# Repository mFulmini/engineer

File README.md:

# engineer
Tutaj znajduje się część pracy inżynierskiej w postaci oprogramowań jednostek brzegowych, rysunków, schematów elektrycznych oraz poglądowych zrzutów ekranu.  This section presents a part of the engineering thesis, comprising edge unit software, technical drawings, electrical schematics, and illustrative screenshots.

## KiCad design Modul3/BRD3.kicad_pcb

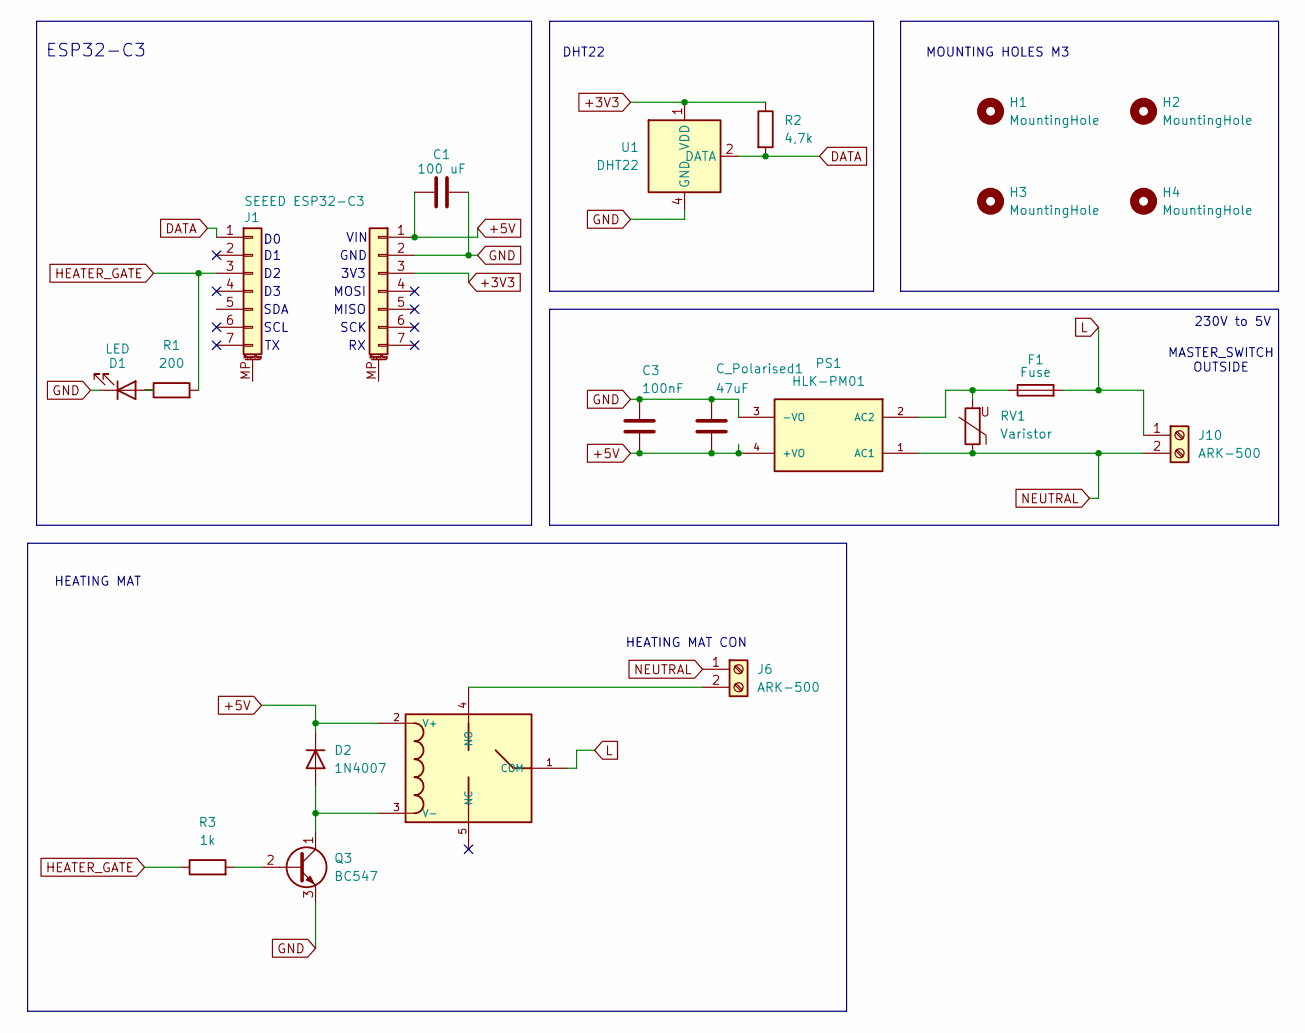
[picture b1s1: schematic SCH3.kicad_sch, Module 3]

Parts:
C1: 100 uF; CP_Radial_D5.0mm_P2.00mm
C3: 100nF; C_Disc_D5.0mm_W2.5mm_P2.50mm
C_Polarised1: 47uF; CP_Radial_D5.0mm_P2.00mm
D1: LED; LED_D5.0mm
D2: 1N4007; D_DO-41_SOD81_P10.16mm_Horizontal
F1: Fuse; Fuseholder_Cylinder-5x20mm_Schurter_FAB_0031-355x_Horizonta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
H1, H2, H3, H4: MountingHole; MountingHole_3.2mm_M3
J1: SEEED ESP32-C3; PinSocket_1x07_P2.54mm_Vertical
J4: Conn_01x07_MountingPin; PinSocket_1x07_P2.54mm_Vertical
J6, J10: ARK-500; TerminalBlock_MaiXu_MX126-5.0-02P_1x02_P5.00mm
K1: RELAY-HLS8L-DC5V-S-C_5P-19X15MM_; REY5-19.0X15.0X15.0MM; MPN HLS8L-DC5V-S-C
PS1: HLK-PM01; Converter_ACDC_Hi-Link_HLK-PMxx
Q3: BC547; TO-92_Inline
R1: 200; R_Axial_DIN0207_L6.3mm_D2.5mm_P5.08mm_Vertical
R2: 4,7k; R_Axial_DIN0207_L6.3mm_D2.5mm_P5.08mm_Vertical
R3: 1k; R_Axial_DIN0207_L6.3mm_D2.5mm_P5.08mm_Vertical
RV1: Varistor; RV_Disc_D9mm_W3.6mm_P5mm
U1: DHT22; PinSocket_1x04_P2.54mm_Vertical

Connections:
+3V3: J4.3, R2.1, U1.1 (VDD)
+5V: C1.1, C3.2, C_Polarised1.2, D2.1 (K), J4.1, K1.2 (V+), PS1.4 (+VO)
DATA: J1.1, R2.2, U1.2 (DATA)
GND: C1.2, C3.1, C_Polarised1.1, D1.1 (K), J4.2, PS1.3 (-VO), Q3.3 (E), U1.4 (GND)
HEATER_GATE: J1.3, R1.2, R3.1
L: F1.2, J10.1, K1.1 (COM)
NEUTRAL: J6.1, J10.2, PS1.1 (AC1), RV1.1
unnamed: D1.2 (A), R1.1
unnamed: D2.2 (A), K1.3 (V-), Q3.1 (C)
unnamed: J6.2, K1.4 (NO)
unnamed: F1.1, PS1.2 (AC2), RV1.2
unnamed: Q3.2 (B), R3.2

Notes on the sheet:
SDA
HEATING MAT
VIN
GND
HEATING MAT CON
MASTER_SWITCH OUTSIDE
SCL
ESP32-C3
DHT22
SCK
MOSI
3V3
MOUNTING HOLES M3
MISO
230V to 5V

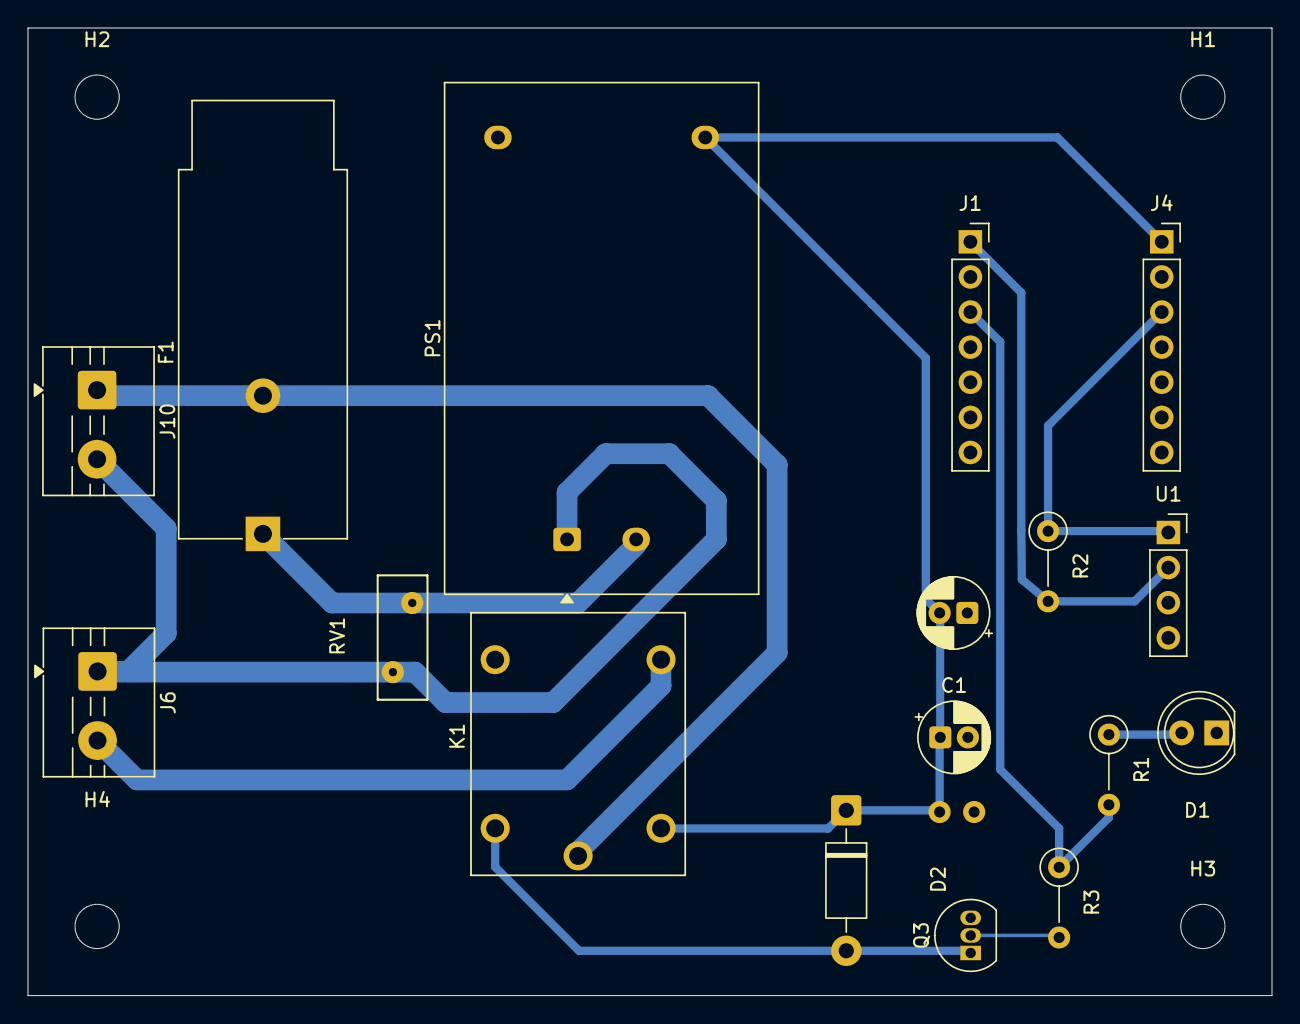
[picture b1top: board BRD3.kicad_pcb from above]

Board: 2 copper layers, 90.0 x 70.0 mm, 22 parts (1 on the bottom side), 12 nets.

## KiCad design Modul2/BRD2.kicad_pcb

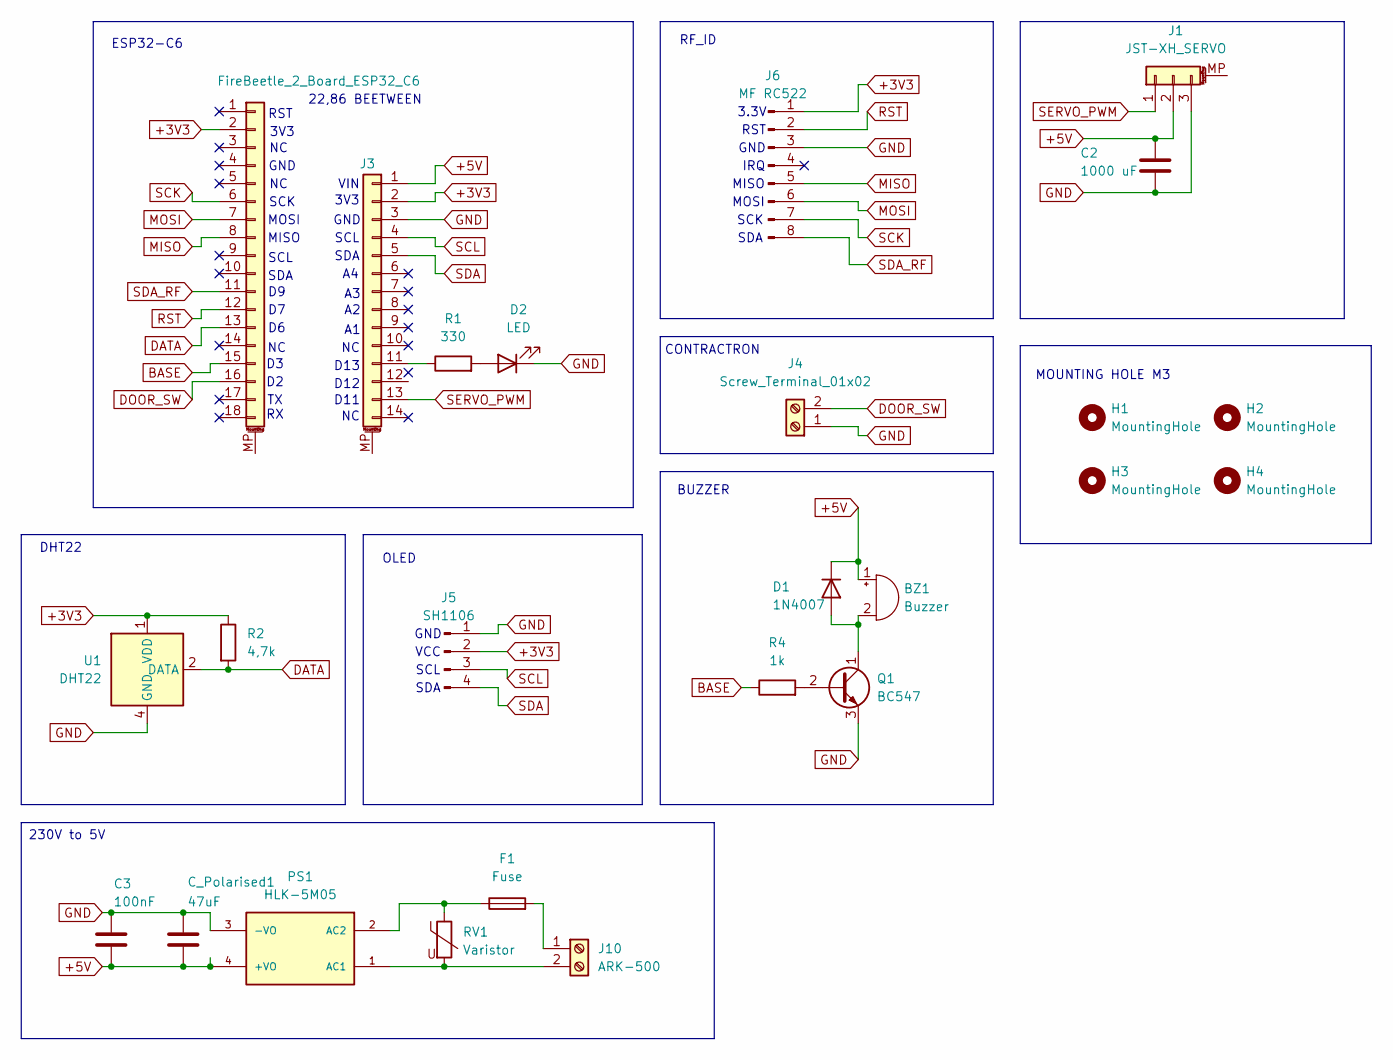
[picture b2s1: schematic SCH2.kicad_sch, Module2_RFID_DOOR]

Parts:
BZ1: Buzzer; Buzzer_12x9.5RM7.6
C2: 1000 uF; CP_Radial_D7.5mm_P2.50mm
C3: 100nF; C_Disc_D3.0mm_W2.0mm_P2.50mm
C_Polarised1: 47uF; CP_Radial_D5.0mm_P2.00mm
D1: 1N4007; D_DO-41_SOD81_P10.16mm_Horizontal
D2: LED; LED_D5.0mm
F1: Fuse; Fuseholder_Cylinder-5x20mm_Schurter_FAB_0031-355x_Horizonta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
H1, H2, H3, H4: MountingHole; MountingHole_3.2mm_M3
J1: JST-XH_SERVO; PinHeader_1x03_P2.54mm_Horizontal
J2: Conn_01x18_MountingPin; PinSocket_1x18_P2.54mm_Vertical
J3: FireBeetle_2_Board_ESP32_C6; PinSocket_1x14_P2.54mm_Vertical
J4: Screw_Terminal_01x02; TerminalBlock_MaiXu_MX126-5.0-02P_1x02_P5.00mm
J5: SH1106; PinSocket_1x04_P2.54mm_Vertical
J6: MF RC522; PinSocket_1x08_P2.54mm_Vertical
J10: ARK-500; TerminalBlock_MaiXu_MX126-5.0-02P_1x02_P5.00mm
PS1: HLK-5M05; Converter_ACDC_Hi-Link_HLK-PMxx
Q1: BC547; TO-92_Inline
R1: 330; R_Axial_DIN0207_L6.3mm_D2.5mm_P10.16mm_Horizontal
R2: 4,7k; R_Axial_DIN0207_L6.3mm_D2.5mm_P7.62mm_Horizontal
R4: 1k; R_Axial_DIN0207_L6.3mm_D2.5mm_P7.62mm_Horizontal
RV1: Varistor; RV_Disc_D12mm_W3.9mm_P7.5mm
U1: DHT22; PinSocket_1x04_P2.54mm_Vertical

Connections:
+3V3: J2.2, J3.2, J5.2, J6.1, R2.1, U1.1 (VDD)
+5V: BZ1.1 (+), C2.1, C3.2, C_Polarised1.2, D1.1 (K), J1.2, J3.1, PS1.4 (+VO)
BASE: J2.15, R4.1
DATA: J2.13, R2.2, U1.2 (DATA)
DOOR_SW: J2.16, J4.2
GND: C2.2, C3.1, C_Polarised1.1, D2.1 (K), J1.3, J3.3, J4.1, J5.1, J6.3, PS1.3 (-VO), Q1.3 (E), U1.4 (GND)
MISO: J2.8, J6.5
MOSI: J2.7, J6.6
unnamed: BZ1.2 (-), D1.2 (A), Q1.1 (C)
unnamed: D2.2 (A), R1.2
unnamed: J3.11, R1.1
unnamed: F1.2, J10.1
unnamed: J10.2, PS1.1 (AC1), RV1.2
unnamed: F1.1, PS1.2 (AC2), RV1.1
unnamed: Q1.2 (B), R4.2
RST: J2.12, J6.2
SCK: J2.6, J6.7
SCL: J3.4, J5.3
SDA: J3.5, J5.4
SDA_RF: J2.11, J6.8
SERVO_PWM: J1.1, J3.13

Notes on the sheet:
VCC
GND
MOUNTING HOLE M3
3V3
IRQ
SCK
ESP32-C6
22,86 BEETWEEN
D13
RF_ID
D11
MOSI
SCL
SDA
BUZZER
CONTRACTRON
RST
GND
SCK
MISO
D12
VIN
OLED
DHT22
3.3V
230V to 5V

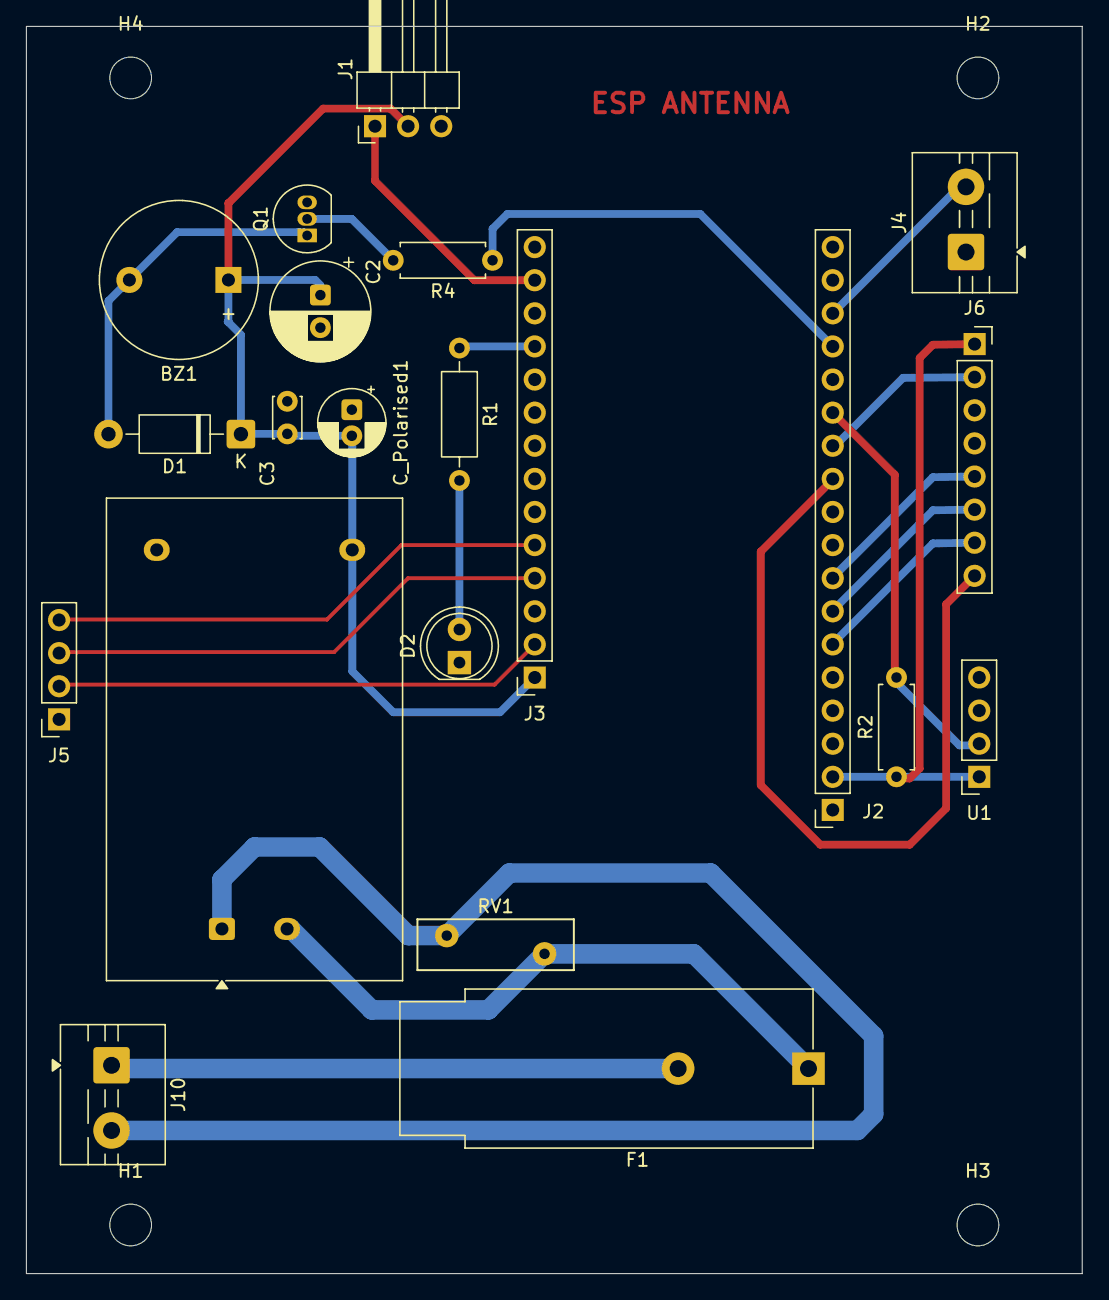
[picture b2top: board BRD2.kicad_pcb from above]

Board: 2 copper layers, 81.0 x 95.7 mm, 25 parts (0 on the bottom side), 21 nets.

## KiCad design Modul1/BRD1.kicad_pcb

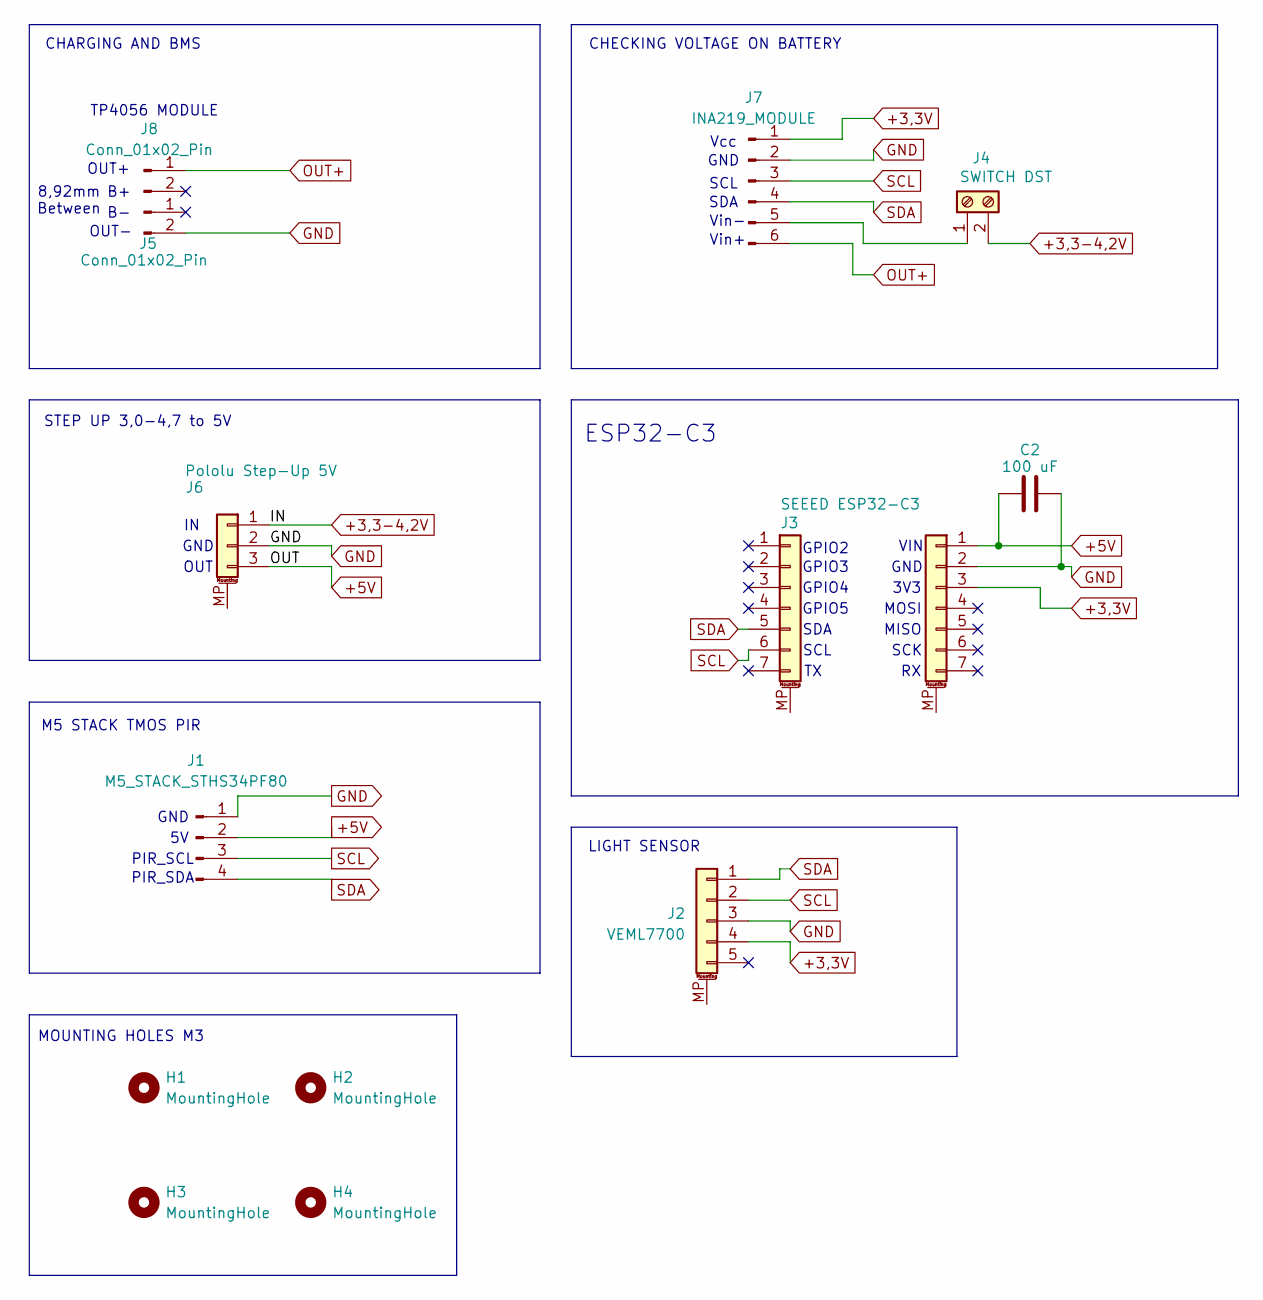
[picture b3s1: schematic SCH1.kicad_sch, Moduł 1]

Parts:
C2: 100 uF; CP_Radial_D5.0mm_P2.00mm
H1, H2, H3, H4: MountingHole; MountingHole_3.2mm_M3
J1: M5_STACK_STHS34PF80; JST_PH_B4B-PH-K_1x04_P2.00mm_Vertical
J2: VEML7700; PinSocket_1x05_P2.54mm_Vertical
J3: SEEED ESP32-C3; PinSocket_1x07_P2.54mm_Vertical
J4: SWITCH DST; TerminalBlock_MaiXu_MX126-5.0-02P_1x02_P5.00mm
J5, J8: Conn_01x02_Pin; PinHeader_1x02_P2.54mm_Vertical
J6: Pololu Step-Up 5V; PinHeader_1x03_P2.54mm_Vertical
J7: INA219_MODULE; PinHeader_1x06_P2.54mm_Vertical
J11: Conn_01x07_MountingPin; PinSocket_1x07_P2.54mm_Vertical

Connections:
+3,3-4,2V: J4.2, J6.1
+3,3V: J2.4, J7.1, J11.3
+5V: C2.1, J1.2, J6.3, J11.1
GND: C2.2, J1.1, J2.3, J5.2, J6.2, J7.2, J11.2
unnamed: J4.1, J7.5
OUT+: J7.6, J8.1
SCL: J1.3, J2.2, J3.6, J7.3
SDA: J1.4, J2.1, J3.5, J7.4

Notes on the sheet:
3V3
8,92mm Between
GND
LIGHT SENSOR
SCL
Vcc
OUT-
MOUNTING HOLES M3
MISO
M5 STACK TMOS PIR
GPIO5
VIN
CHARGING AND BMS
Vin+
SDA
MOSI
GPIO2
STEP UP 3,0-4,7 to 5V
ESP32-C3
TP4056 MODULE
PIR_SCL
OUT+
SCK
GPIO3
OUT
Vin-
PIR_SDA
GPIO4
CHECKING VOLTAGE ON BATTERY

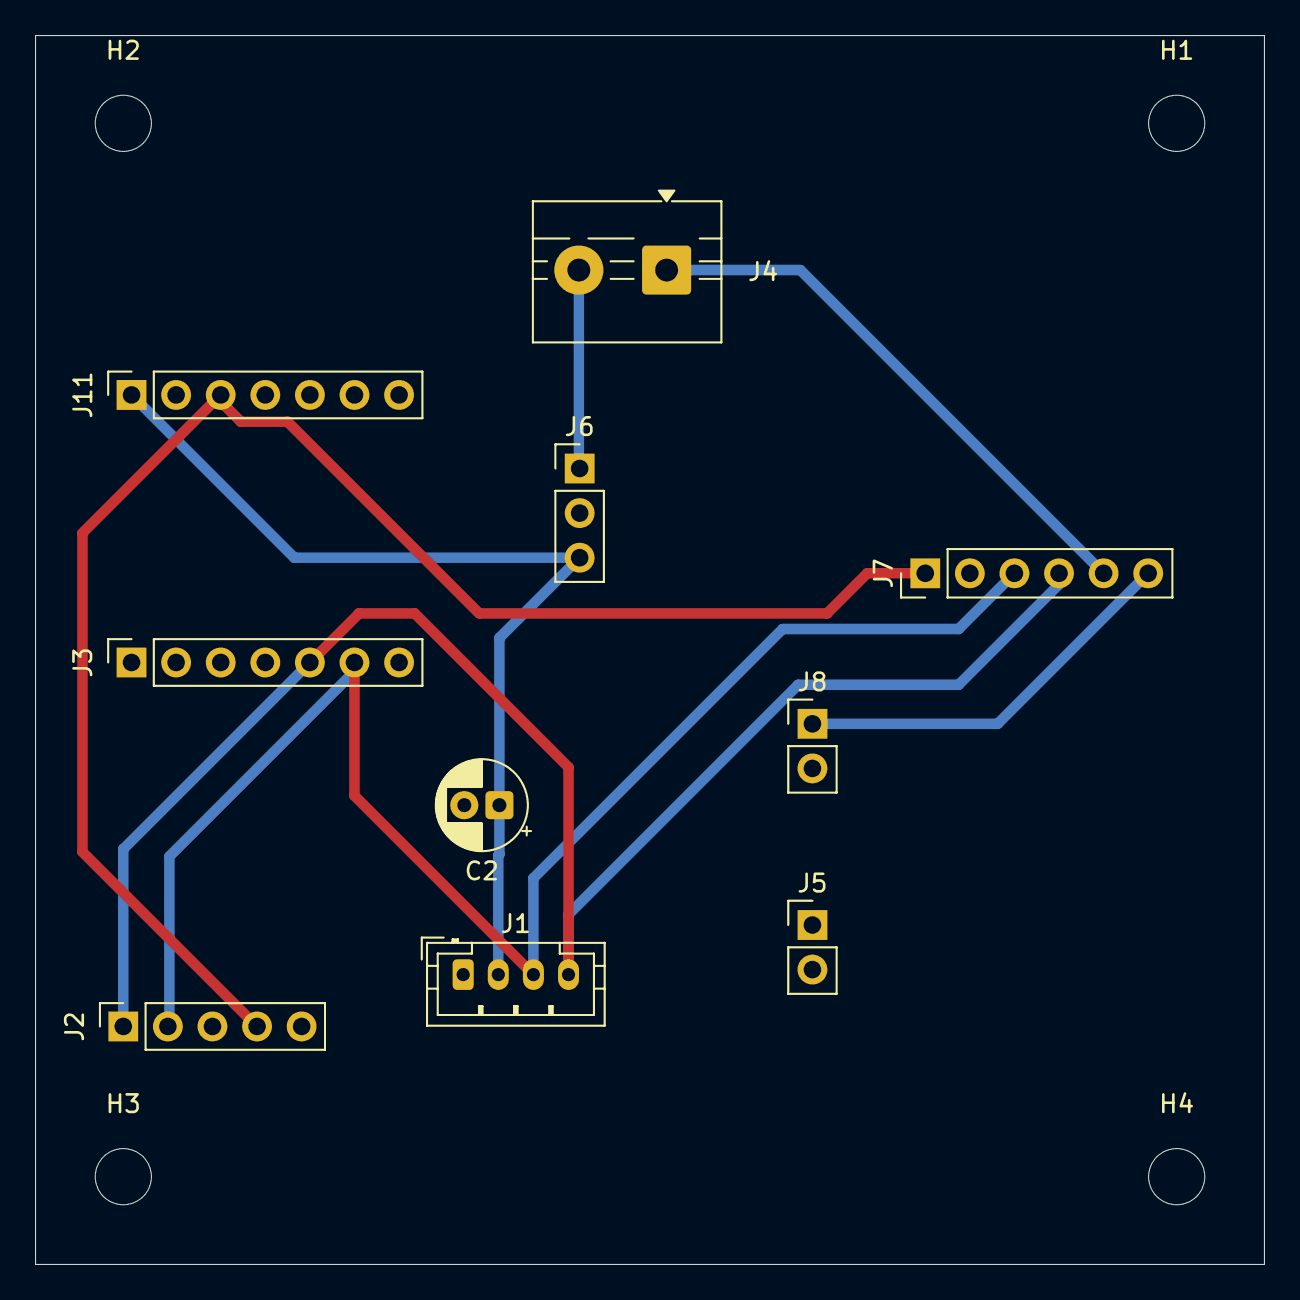
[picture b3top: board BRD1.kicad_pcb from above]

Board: 2 copper layers, 70.0 x 70.0 mm, 14 parts (0 on the bottom side), 8 nets.

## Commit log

2026-01-28 Create tpl
